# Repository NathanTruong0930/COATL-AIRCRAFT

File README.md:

# COATL-AIRCRAFT

## Team 3 Members:
- Felix Moss
- Annika Boyd
- Eisa Alsharifi
- Nathan Truong

---

### Project: Electrostatic Dust Analyzer

This repository contains code and resources for the **Electrostatic Dust Analyzer** project developed as part of the PSU Capstone program. This project utilizes a QT PY ESP32 Development Board to interpret current measurements taken from dust particles for use in determining air conditions. 

---

### Key Features

1. **Real-Time Detection of Charged Particles**

    Detects volcanic ash, mineral dust, and wildfire smoke using induced charge measurements.

2. **Electrostatic Sensing Technology**

    Uses a Faraday tube and wire electrodes to sense small electrical currents from passing particles.

3. **Wireless Data Transmission**

    The QT PY ESP32 Development Board transmits measurements via Wi-Fi to a web interface for real-time monitoring.

4. **Onboard Signal Processing**

    Calculates induced charge and estimates particle size based on charge density assumptions.

5. **Multi-Stage Gain Amplifier**

    Manually switchable gain stages (3.9×, 15×, 47×) allow for a wide range of signal amplitudes.

6. **Web Interface for Visualization**

    Displays live data including voltage, charge, gain level, and particle size.

7. **Compact, Low-Power Design**

    Operates on a 9V battery at ~1.35 W, suitable for eventual aircraft integration.

8. **Lab-Tested with Real Volcanic Ash**

    Validated through controlled experiments using Mt. St. Helens ash samples.

---

### Repository Overview

- **412_Practicum:** Assignments and other in class documents
- **Bill_of_Materials:** List of components used in the project
- **Fusion_Files:** PCB box fusion files
- **Gantt_Chart:** Project Gantt chart
- **Kicad:** All project KiCAD files
- **LTSpice_Simulation:** All LTSpice files
- **Research_Documents:** Documents and notes used for research purposes
- **Team_Meeting_Notes:** Notes from team meetings and discussions
- **Testing_Documentation:** Documentation of tests run by the team
- **Weekly_Progress_Report:** Weekly log of progress by the team

---

### Notes

- The files present in the **KiCAD** folder are of older designs and are not of the final PCB enclosure, which was provided by our sponsor Josh Méndez.
- 

---

### License:

This project is licensed under the [GPL-3.0 license](LICENSE).

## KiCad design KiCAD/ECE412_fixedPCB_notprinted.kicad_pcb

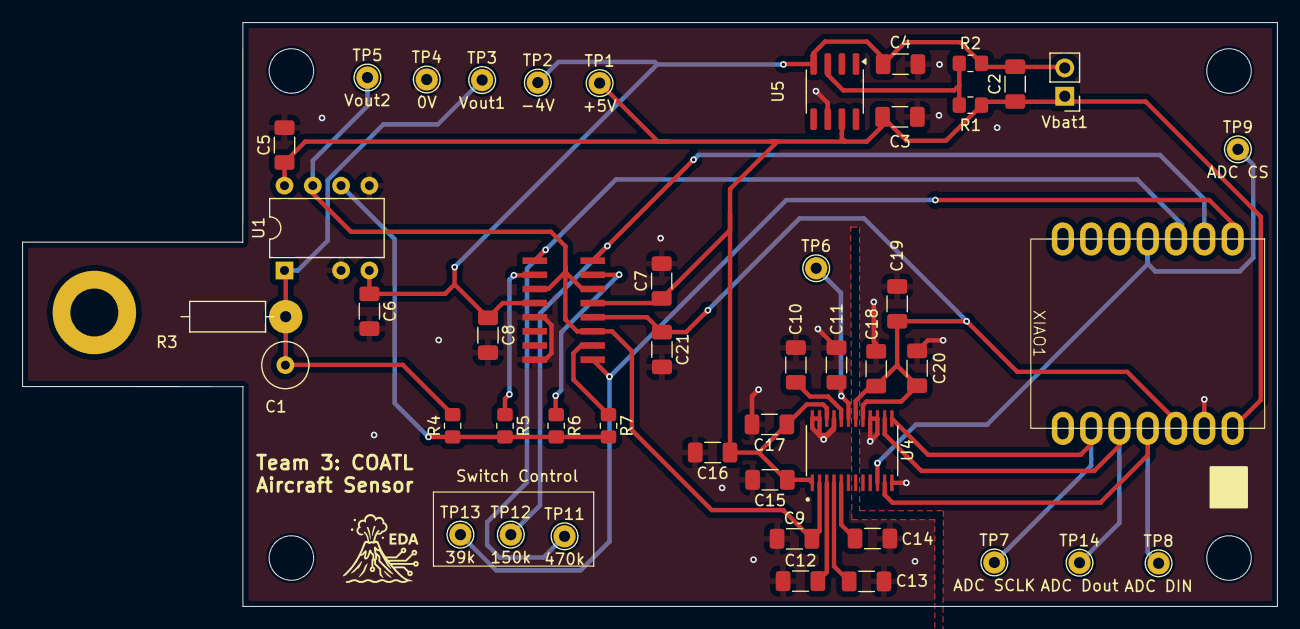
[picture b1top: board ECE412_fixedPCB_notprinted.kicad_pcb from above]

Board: 2 copper layers, 112.7 x 52.4 mm, 47 parts (0 on the bottom side), 23 nets.

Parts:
C1: 100p; C_Radial_D10.0mm_H12.5mm_P5.00mm
C2, C3, C4, C16: 10uF; C_1206_3216Metric_Pad1.33x1.80mm_HandSolder
C5, C6, C7, C8, C12, C13, C14, C15, C17, C18, C20, C21: 0.1uF; C_1206_3216Metric_Pad1.33x1.80mm_HandSolder
C9: 100pF; C_1206_3216Metric_Pad1.33x1.80mm_HandSolder
C10, C11, C19: 1uF; C_1206_3216Metric_Pad1.33x1.80mm_HandSolder
IC1: ADG412; SOIC16N
R1, R4: 10k; R_0805_2012Metric_Pad1.20x1.40mm_HandSolder
R2: 6k; R_0805_2012Metric_Pad1.20x1.40mm_HandSolder
R3: 5G; R_Vishay_TR10X5G00JNES
R5: 470k; R_0805_2012Metric_Pad1.20x1.40mm_HandSolder
R6: 150k; R_0805_2012Metric_Pad1.20x1.40mm_HandSolder
R7: 39k; R_0805_2012Metric_Pad1.20x1.40mm_HandSolder
TP1: +5V; TestPoint_THTPad_D2.0mm_Drill1.0mm
TP2: -4V; TestPoint_THTPad_D2.0mm_Drill1.0mm
TP3: Vout1; TestPoint_THTPad_D2.0mm_Drill1.0mm
TP4: 0V; TestPoint_THTPad_D2.0mm_Drill1.0mm
TP5: Vout2; TestPoint_THTPad_D2.0mm_Drill1.0mm
TP6: ADC Vref; TestPoint_THTPad_D2.0mm_Drill1.0mm
TP7: ADC SCLK; TestPoint_THTPad_D2.0mm_Drill1.0mm
TP8: ADC DIN; TestPoint_THTPad_D2.0mm_Drill1.0mm
TP9: ADC CS; TestPoint_THTPad_D2.0mm_Drill1.0mm
TP11: 470k; TestPoint_THTPad_D2.0mm_Drill1.0mm
TP12: 150k; TestPoint_THTPad_D2.0mm_Drill1.0mm
TP13: 39k; TestPoint_THTPad_D2.0mm_Drill1.0mm
TP14: ADC Dout; TestPoint_THTPad_D2.0mm_Drill1.0mm
U1: LMC662; DIP-8_W7.62mm
U4: MAX1032BEUG_; SOP65P640X110-24N
U5: BUF634AxD; SOIC-8_3.9x4.9mm_P1.27mm
Vbat1: 9V; PinHeader_1x02_P2.54mm_Vertical
XIAO1: XIAO_QTpy

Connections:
/3.3V: C18.2, C19.1, C20.2, C21.1, IC1.12 (VL), U4.17 (DVDD0), U4.18 (DVDD), XIAO1.3V3
/+5V: C2.1, C3.1, C5.1, C7.1, C15.1, C16.1, C17.1, IC1.13 (VDD), R1.1, TP1.1, U1.8 (V+), U4.1 (AVDD1), U4.22 (AVDD2), U5.7 (V+), Vbat1.1 (+), XIAO1.5V
/-4V: C2.2, C4.2, C6.1, C8.1, IC1.4 (VSS), R2.2, TP2.1, U1.4 (V-), U5.4 (V-), Vbat1.2 (-)
GND: C3.2, C4.1, C5.2, C6.2, C7.2, C8.2, C9.1, C10.1, C11.2, C12.1, C13.1, C14.1, C15.2, C16.2, C17.2, C18.1, C19.2, C20.1, C21.2, IC1.5 (GND), IC1.8, TP4.1, U1.3 (POSA), U1.5 (POSB), U4.12 (SSTRB), U4.15 (DGND0), U4.16 (DGND), U4.21 (AGND3), U4.23 (AGND2), U4.24 (AGND1), U5.6, XIAO1.GND
unnamed: IC1.1, TP11.1, XIAO1.2
unnamed: IC1.2, R5.1
unnamed: IC1.9, TP13.1, XIAO1.0
unnamed: IC1.10, R7.1
unnamed: IC1.15, R6.1
unnamed: IC1.16, TP12.1, XIAO1.1
unnamed: R4.1, R5.2, R6.2, R7.2, U1.6 (NEGB)
unnamed: C1.1, R3.1, R4.2, TP3.1, U1.1 (OUTA)
unnamed: C9.2, IC1.3, IC1.11, IC1.14, TP5.1, U1.7 (OUTB), U4.2 (CH0)
unnamed: C12.2, U4.3 (CH1)
unnamed: C13.2, U4.4 (CH2)
unnamed: C14.2, U4.5 (CH3)
unnamed: TP8.1, U4.11 (DIN), XIAO1.10
unnamed: TP14.1, U4.14 (DOUT), XIAO1.9
unnamed: C10.2, U4.20 (REF)
unnamed: C11.1, TP6.1, U4.19 (REFCAP)
unnamed: TP7.1, U4.13 (SCLK), XIAO1.8
unnamed: TP9.1, U4.10 (~CS), XIAO1.3
unnamed: R1.2, R2.1, U5.3 (V_{IN})

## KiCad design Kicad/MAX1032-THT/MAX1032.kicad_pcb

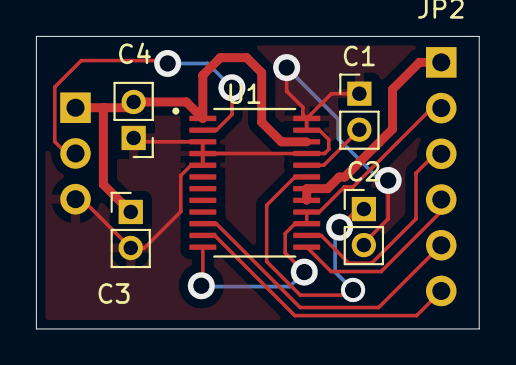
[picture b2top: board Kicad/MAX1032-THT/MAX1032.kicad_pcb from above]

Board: 2 copper layers, 24.6 x 16.2 mm, 7 parts (0 on the bottom side), 11 nets.

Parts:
C1, C3: 0.1uF; PinHeader_1x02_P2.00mm_Vertical
C2: 1uF; PinHeader_1x02_P2.00mm_Vertical
C4: 10uF; PinHeader_1x02_P2.00mm_Vertical
JP1: HEADER-1X3; PinHeader_1x03_P2.54mm_Horizontal
JP2: HEADER-1X6; PinHeader_1x06_P2.54mm_Horizontal
U1: MAX1032BEUG_; SOP65P640X110-24N

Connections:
/AVDD: C3.1, C4.2, JP1.1, U1.1 (AVDD1), U1.22 (AVDD2)
/CH0: JP1.2, U1.2 (CH0)
/CS*: JP2.5, U1.10 (~CS)
/DGND: JP2.2, U1.12 (SSTRB), U1.15 (DGND0), U1.16 (DGND)
/DIN: JP2.6, U1.11 (DIN)
/DOUT: JP2.3, U1.14 (DOUT)
/DVDD: JP2.1, U1.17 (DVDD0), U1.18 (DVDD)
/SCLK: JP2.4, U1.13 (SCLK)
GND: C1.1, C2.2, C3.2, C4.1, JP1.3, U1.3 (CH1), U1.4 (CH2), U1.5 (CH3), U1.21 (AGND3), U1.23 (AGND2), U1.24 (AGND1)
unnamed: C1.2, U1.20 (REF)
unnamed: C2.1, U1.19 (REFCAP)

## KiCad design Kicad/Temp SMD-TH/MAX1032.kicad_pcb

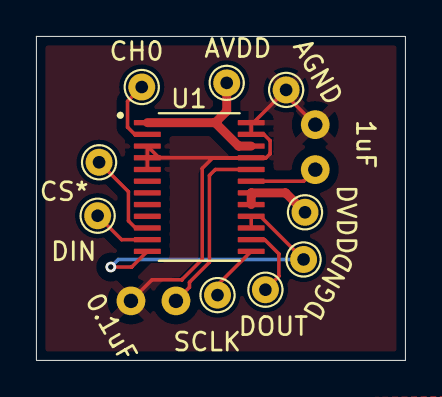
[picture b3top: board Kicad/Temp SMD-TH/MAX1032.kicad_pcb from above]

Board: 2 copper layers, 20.5 x 18.0 mm, 12 parts (0 on the bottom side), 11 nets.

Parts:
AGND: TestPoint_THTPad_D1.5mm_Drill0.7mm
AVDD: TestPoint; TestPoint_THTPad_D1.5mm_Drill0.7mm
C1: 0.1uF; C_Radial_D6.3mm_H5.0mm_P2.50mm
C2: 1uF; C_Radial_D6.3mm_H5.0mm_P2.50mm
CH0: TestPoint; TestPoint_THTPad_D1.5mm_Drill0.7mm
CS*: TestPoint; TestPoint_THTPad_D1.5mm_Drill0.7mm
DGND: TestPoint_THTPad_D1.5mm_Drill0.7mm
DIN: TestPoint; TestPoint_THTPad_D1.5mm_Drill0.7mm
DOUT: TestPoint; TestPoint_THTPad_D1.5mm_Drill0.7mm
DVDD: TestPoint; TestPoint_THTPad_D1.5mm_Drill0.7mm
SCLK: TestPoint; TestPoint_THTPad_D1.5mm_Drill0.7mm
U1: MAX1032BEUG_; SOP65P640X110-24N

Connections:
GND: AGND.1, C1.1, C2.2, U1.3 (CH1), U1.4 (CH2), U1.5 (CH3), U1.21 (AGND3), U1.23 (AGND2), U1.24 (AGND1)
unnamed: AVDD.1, U1.1 (AVDD1), U1.22 (AVDD2)
unnamed: CH0.1, U1.2 (CH0)
unnamed: DGND.1, U1.12 (SSTRB), U1.15 (DGND0), U1.16 (DGND)
unnamed: DIN.1, U1.11 (DIN)
unnamed: DOUT.1, U1.14 (DOUT)
unnamed: DVDD.1, U1.17 (DVDD0), U1.18 (DVDD)
unnamed: C1.2, U1.20 (REF)
unnamed: C2.1, U1.19 (REFCAP)
unnamed: SCLK.1, U1.13 (SCLK)
unnamed: CS*.1, U1.10 (~CS)

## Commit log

2025-01-08 Created Weekly Progress Report
2025-01-13 Update Weekly Progress Report
2025-01-13 Create LICENSE
2025-01-16 Week 2 Progress Update
2025-01-19 Added organizational folders, team meeting notes, and external resources/research
2025-01-19 Uploaded Team Check-in Notes
2025-01-24 Added Audio Files
2025-01-24 Deleted .vscode file
2025-01-26 Update LICENSE
2025-01-31 Create a
2025-01-31 Weekly Progress Update
2025-02-02 Rename png2pdf (2).pdf to Preliminary Schematic
2025-02-02 Rename Screenshot 2025-02-02 145736.png to Preliminary Schematic
2025-02-03 Rename png2pdf (2).pdf to Preliminary Schematic.pdf
2025-02-05 Added Ted Talk #2, Team Meeting Notes, 02/02 purchase order, and a Link to the BOM
2025-02-05 Formatting
2025-02-10 Updated Weekly Progress Report, Added team check-in notes
2025-02-12 Uploaded Team Meeting Notes 02_12_25
2025-02-18 Added team check-in notes, updated weekly progress report
2025-02-20 Rename Schematic/Preliminary Schematic.pdf to Preliminary Schematic.pdf
2025-02-20 Rename Schematic/Rough Draft Schematic.pdf to Rough Draft Schematic.pdf
2025-02-20 Rename Preliminary Schematic.pdf to Kicad/Schematic/Preliminary Schematic.pdf
2025-02-20 Rename Rough Draft Schematic.pdf to Kicad/Schematic/Rough Draft Schematic.pdf
2025-02-23 Rename Kicad/LMC662AIMX_NOPB.zip to Kicad/Footprints/LMC662AIMX_NOPB.zip
2025-02-23 Rename Kicad/MAX1032BEUG_.lib to Kicad/Footprints/MAX1032BEUG_.lib
2025-02-23 Rename Kicad/LMC6042IM.lib to Kicad/Footprints/LMC6042IM.lib
2025-02-24 Added team meeting and team check-in notes, Fixed a typo in 2/12 meeting notes, Added breadboard test documentation, Updated weekly progress report
2025-02-26 Rename Kicad/MAX1032.kicad_pro to Kicad/Temp SMD-TH/MAX1032.kicad_pro
2025-03-04 Rename Kicad/MAX1032.kicad_pro to Kicad/MAX1032-THT/MAX1032.kicad_pro
2025-03-04 Rename AIRcraft_purchase_order-2-18.pdf to Purchase Order 02_18_25.pdf
2025-03-05 Updated weekly progress report, Team check-in notes added, Team meeting notes added
2025-03-12 Updated weekly progress report, Added team meeting notes, Updated README
2025-03-18 Updated weekly progress report, Added team meeting and team check-in notes, Added fusion files for PCB box
2025-04-06 Added Ted Talk, Check in notes, and Team Meeting Notes
2025-04-06 Weekly progress updates
2025-04-07 Create Mian
2025-04-07 Rename Mian to Main
2025-04-07 Create QT-Py
2025-04-07 Uploaded team meeting notes
2025-04-09 Update QT-Py
2025-04-16 Updated weekly progress report, Added team meeting notes, Added team check-in notes
2025-04-17 Added team meeting notes
2025-04-21 Update Main
2025-04-27 Updated weekly progress report, Added newest fusion files, Added team meeting notes
2025-05-08 Create Bit range gain code
2025-05-11 Updated weekly progress report, Added team meeting notes
2025-05-15 Create Main_ADG(test)
2025-05-16 Update Main_ADG(test)
2025-05-22 Update Main_ADG(test)
    added way to see it through a website
2025-05-26 Create WiFi(test)
2025-05-27 Updated weekly progress report, added team meeting notes, added test results
2025-05-27 Update WiFi(test)
2025-05-27 Added final PCB Box Files
2025-05-29 Create Surface Charge Density Sources
2025-06-06 Create manual_switchingwebsite
2025-06-06 Create manualswitching_continuousdata&plot_website
2025-06-07 Update manualswitching_continuousdata&plot_website
2025-06-08 Update Weekly Progress Report Term 2
2025-06-11 Updated weekly progress report
2025-06-11 File renaming, README modifications
2025-06-11 README Changes
2025-06-11 Added team meeting notes, Added ethics assignment
2025-06-11 Added test plans
2025-06-12 Rename Schematic.pdf to Final Schematic.pdf
2025-06-16 Create EDA_CODE_FINAL
2025-06-16 Add files via upload
    fixed: B.Mask cutout, TP names on wrong layer
2025-06-16 added mt.saint helens published particle sizes
2025-06-18 Create Test Data
